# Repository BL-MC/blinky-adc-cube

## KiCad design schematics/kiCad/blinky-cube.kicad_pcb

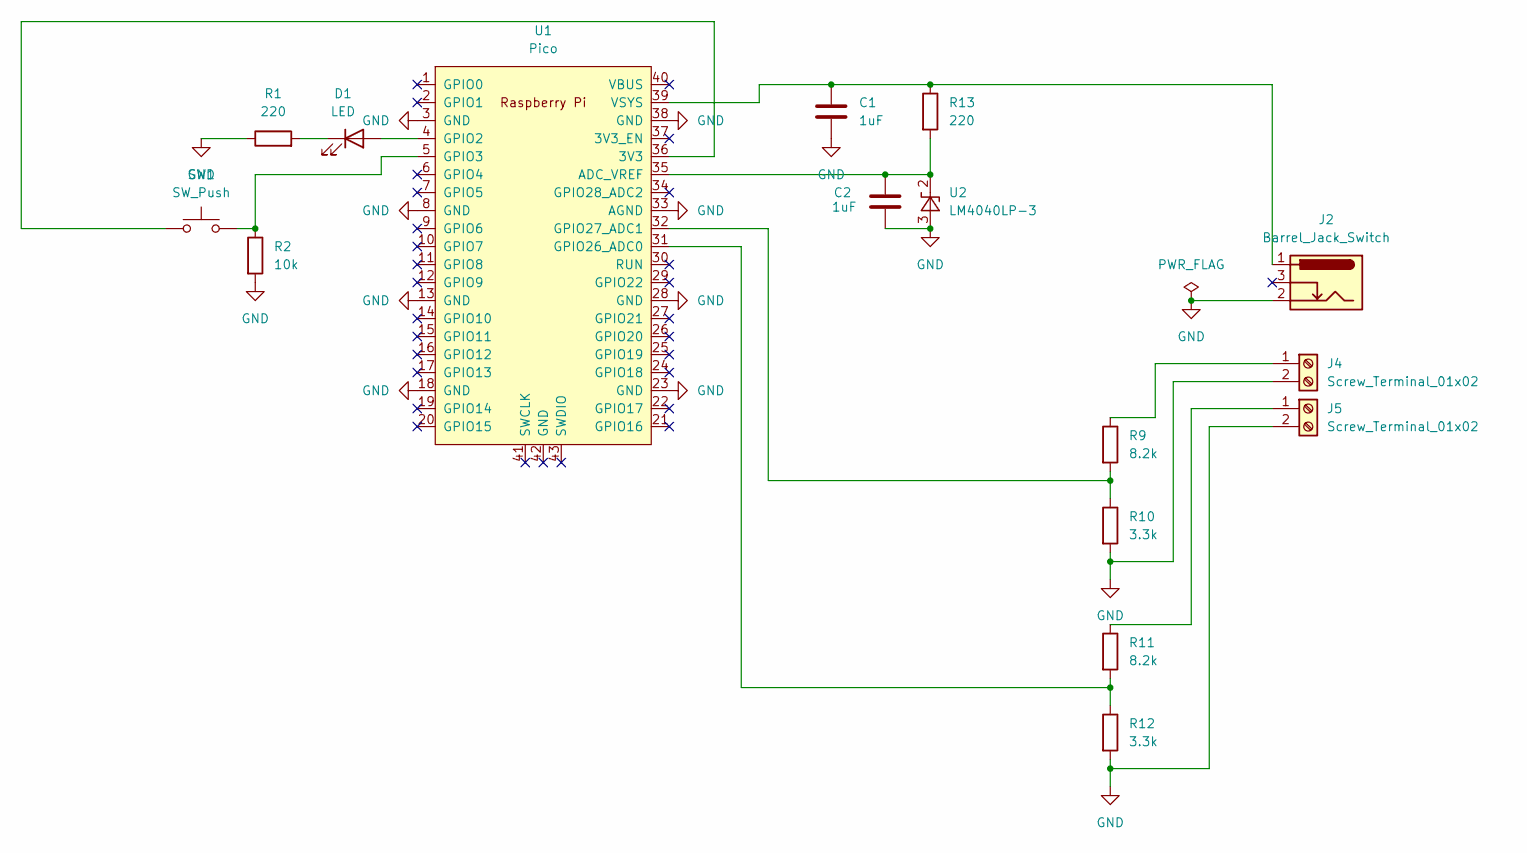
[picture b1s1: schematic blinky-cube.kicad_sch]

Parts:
C1, C2: 1uF; C_Disc_D4.7mm_W2.5mm_P5.00mm
D1: LED; LED_D5.0mm
J2: Barrel_Jack_Switch; BarrelJack_Horizontal
J4, J5: Screw_Terminal_01x02; TerminalBlock_Phoenix_MKDS-3-2-5.08_1x02_P5.08mm_Horizontal
R1, R13: 220; R_Axial_DIN0207_L6.3mm_D2.5mm_P7.62mm_Horizontal
R2: 10k; R_Axial_DIN0207_L6.3mm_D2.5mm_P7.62mm_Horizontal
R9, R11: 8.2k; R_Axial_DIN0207_L6.3mm_D2.5mm_P7.62mm_Horizontal
R10, R12: 3.3k; R_Axial_DIN0207_L6.3mm_D2.5mm_P7.62mm_Horizontal
SW1: SW_Push; SW_PUSH_6mm
U1: Pico; RPi_Pico_SMD_TH
U2: LM4040LP-3; TO-92_Inline

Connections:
GND: C1.2, C2.2, J2.2, J4.2, J5.2, R1.1, R2.2, R10.2, R12.2, U1.3 (GND), U1.8 (GND), U1.13 (GND), U1.18 (GND), U1.23 (GND), U1.28 (GND), U1.33 (AGND), U1.38 (GND), U2.3 (A)
unnamed: D1.2 (A), U1.4 (GPIO2)
unnamed: D1.1 (K), R1.2
unnamed: J4.1, R9.1
unnamed: J5.1, R11.1
unnamed: SW1.1, U1.36 (3V3)
unnamed: C2.1, R13.2, U1.35 (ADC_VREF), U2.2 (K)
unnamed: R2.1, SW1.2, U1.5 (GPIO3)
unnamed: R11.2, R12.1, U1.31 (GPIO26_ADC0)
unnamed: R9.2, R10.1, U1.32 (GPIO27_ADC1)
unnamed: C1.1, J2.1, R13.1, U1.39 (VSYS)

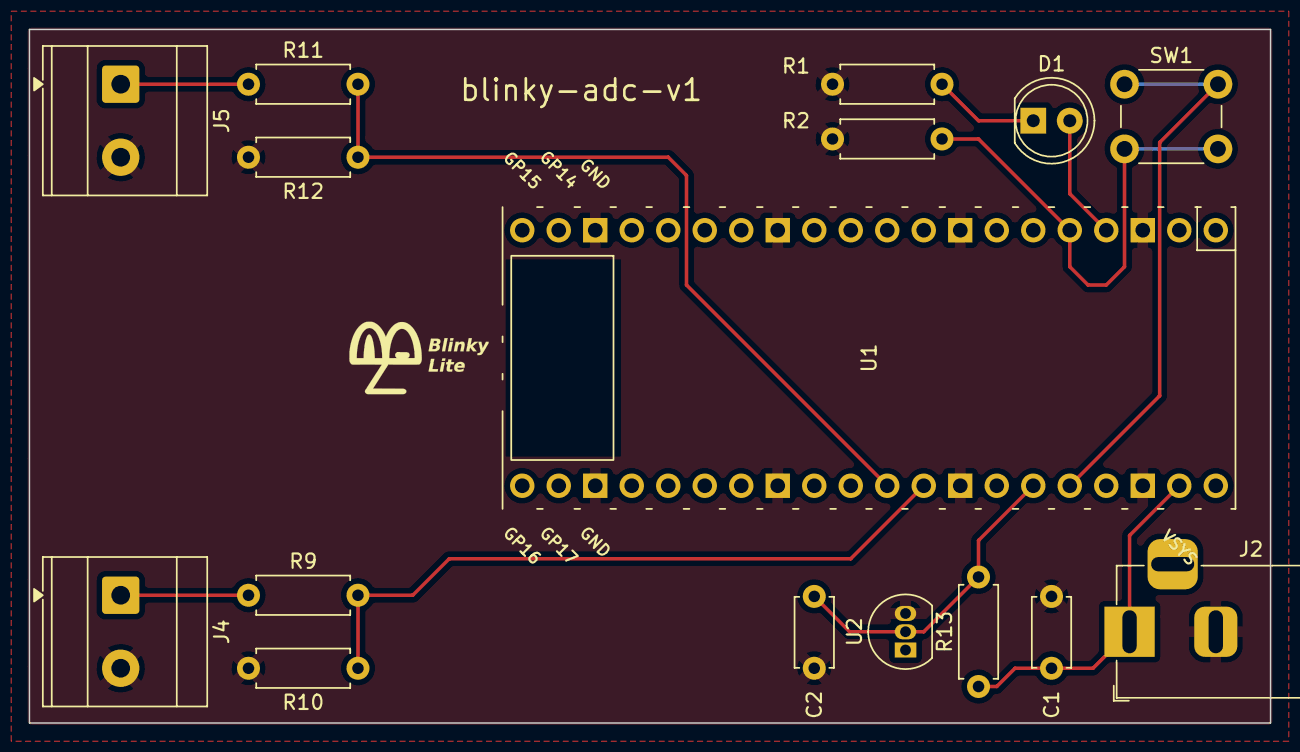
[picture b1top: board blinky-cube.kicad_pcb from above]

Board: 2 copper layers, 86.4 x 48.3 mm, 16 parts (0 on the bottom side), 11 nets.
